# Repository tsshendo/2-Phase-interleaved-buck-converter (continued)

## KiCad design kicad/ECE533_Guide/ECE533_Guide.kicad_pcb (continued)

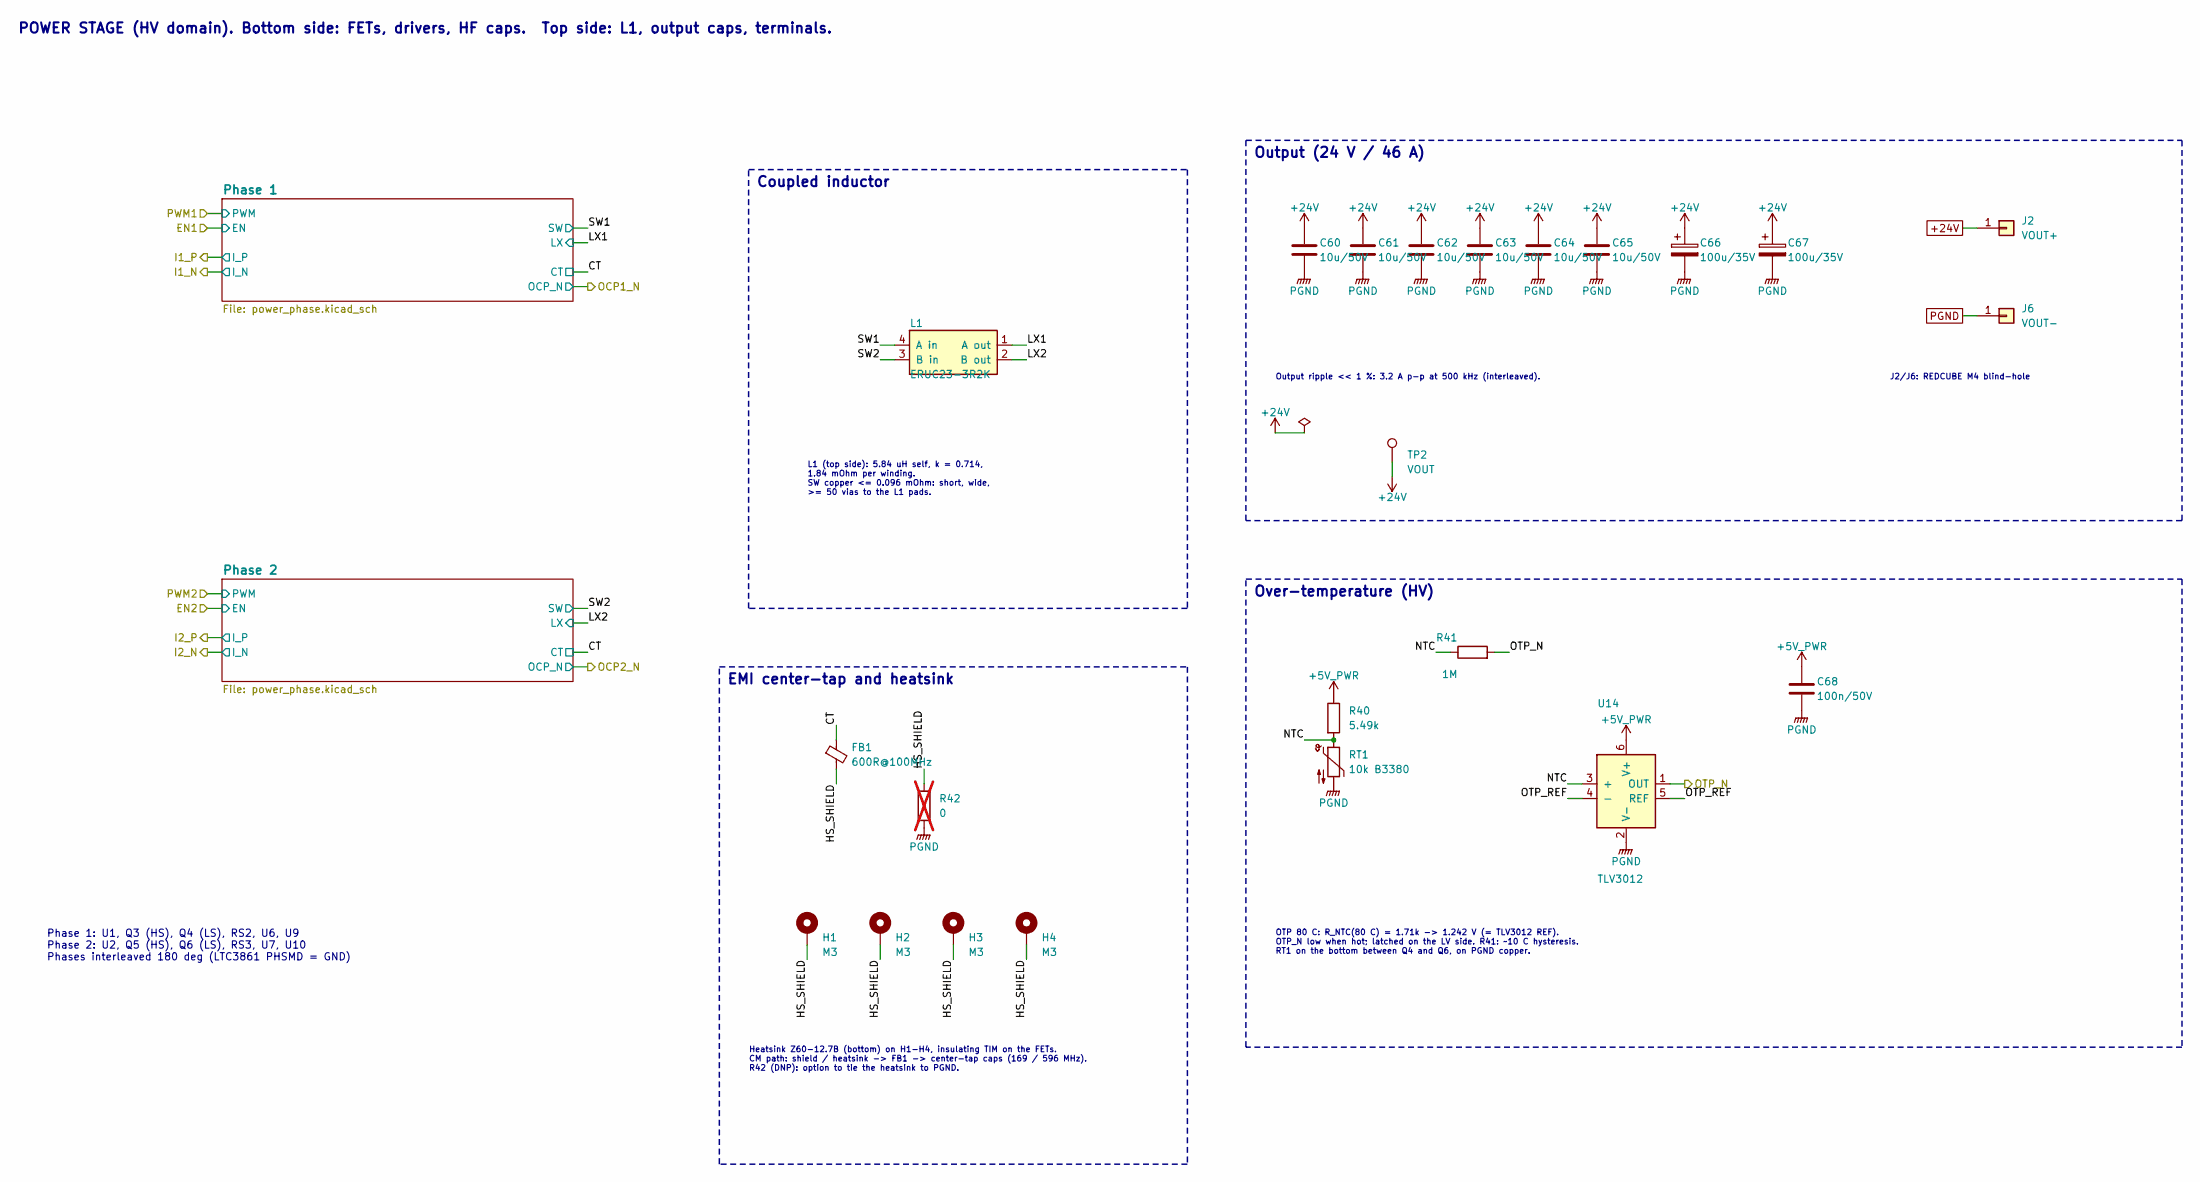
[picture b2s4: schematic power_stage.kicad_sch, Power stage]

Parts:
C60, C61, C62, C63, C64, C65: 10u/50V; C_1210_3225Metric; MPN GRM32ER71H106KA12L; LCSC C77102
C66, C67: 100u/35V; CP_Elec_8x10.5; MPN EEH-ZA1V101P
C68: 100n/50V; C_0603_1608Metric; MPN GRM188R71H104KA93D; LCSC C77055
FB1: 600R@100MHz; L_0603_1608Metric; MPN BLM18KG601SN1D; LCSC C85833
H1, H2, H3, H4: M3; MountingHole_3.2mm_M3_Pad_Via; MPN M3 plated hole
J2: VOUT+; Wurth_REDCUBE_74650194; MPN 74650194R
J6: VOUT-; Wurth_REDCUBE_74650194; MPN 74650194R
L1: ERUC23-3R2K; TDK_ERUC23; MPN ERUC23-3R2K
R40: 5.49k; R_0603_1608Metric; MPN RC0603FR-075K49L
R41: 1M; R_0603_1608Metric; MPN RC0603FR-071ML
R42: 0; R_0603_1608Metric; MPN RC0603JR-070RL; not fitted
RT1: 10k B3380; R_0603_1608Metric; MPN NCP18XH103F03RB; LCSC C13564
TP2: VOUT; TestPoint_Pad_D1.0mm; MPN Test pad (bare copper)
U14: TLV3012; SOT-23-6; MPN TLV3012AIDBVR; LCSC C62505

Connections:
+5V_PWR: C68.1, R40.1, U14.6 (V+); also elsewhere on the board
+24V: C60.1, C61.1, C62.1, C63.1, C64.1, C65.1, C66.1, C67.1, J2.1, TP2.1; also elsewhere on the board
/OTP_N: R41.2, U14.1 (OUT); also elsewhere on the board
/Power stage (2 phases)/CT: FB1.1; also elsewhere on the board
/Power stage (2 phases)/HS_SHIELD: FB1.2, H1.1, H2.1, H3.1, H4.1, R42.1
/Power stage (2 phases)/LX1: L1.1 (A out); also elsewhere on the board
/Power stage (2 phases)/LX2: L1.2 (B out); also elsewhere on the board
/Power stage (2 phases)/NTC: R40.2, R41.1, RT1.1, U14.3 (+)
/Power stage (2 phases)/OTP_REF: U14.4 (-), U14.5 (REF)
/Power stage (2 phases)/SW1: L1.4 (A in); also elsewhere on the board
/Power stage (2 phases)/SW2: L1.3 (B in); also elsewhere on the board
PGND: C60.2, C61.2, C62.2, C63.2, C64.2, C65.2, C66.2, C67.2, C68.2, J6.1, R42.2, RT1.2, U14.2 (V-); also elsewhere on the board

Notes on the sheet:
POWER STAGE (HV domain). Bottom side: FETs, drivers, HF caps. Top side: L1, output caps, terminals.
Phase 1: U1, Q3 (HS), Q4 (LS), RS2, U6, U9 Phase 2: U2, Q5 (HS), Q6 (LS), RS3, U7, U10 Phases interleaved 180 deg (LTC3861 PHSMD = GND)
L1 (top side): 5.84 uH self, k = 0.714, 1.84 mOhm per winding. SW copper <= 0.096 mOhm: short, wide, >= 50 vias to the L1 pads.
Coupled inductor
Output ripple << 1 %: 3.2 A p-p at 500 kHz (interleaved).
J2/J6: REDCUBE M4 blind-hole
Output (24 V / 46 A)
OTP 80 C: R_NTC(80 C) = 1.71k -> 1.242 V (= TLV3012 REF). OTP_N low when hot; latched on the LV side. R41: ~10 C hysteresis. RT1 on the bottom between Q4 and Q6, on PGND copper.
Over-temperature (HV)
Heatsink Z60-12.7B (bottom) on H1-H4, insulating TIM on the FETs. CM path: shield / heatsink -> FB1 -> center-tap caps (169 / 596 MHz). R42 (DNP): option to tie the heatsink to PGND.
EMI center-tap and heatsink

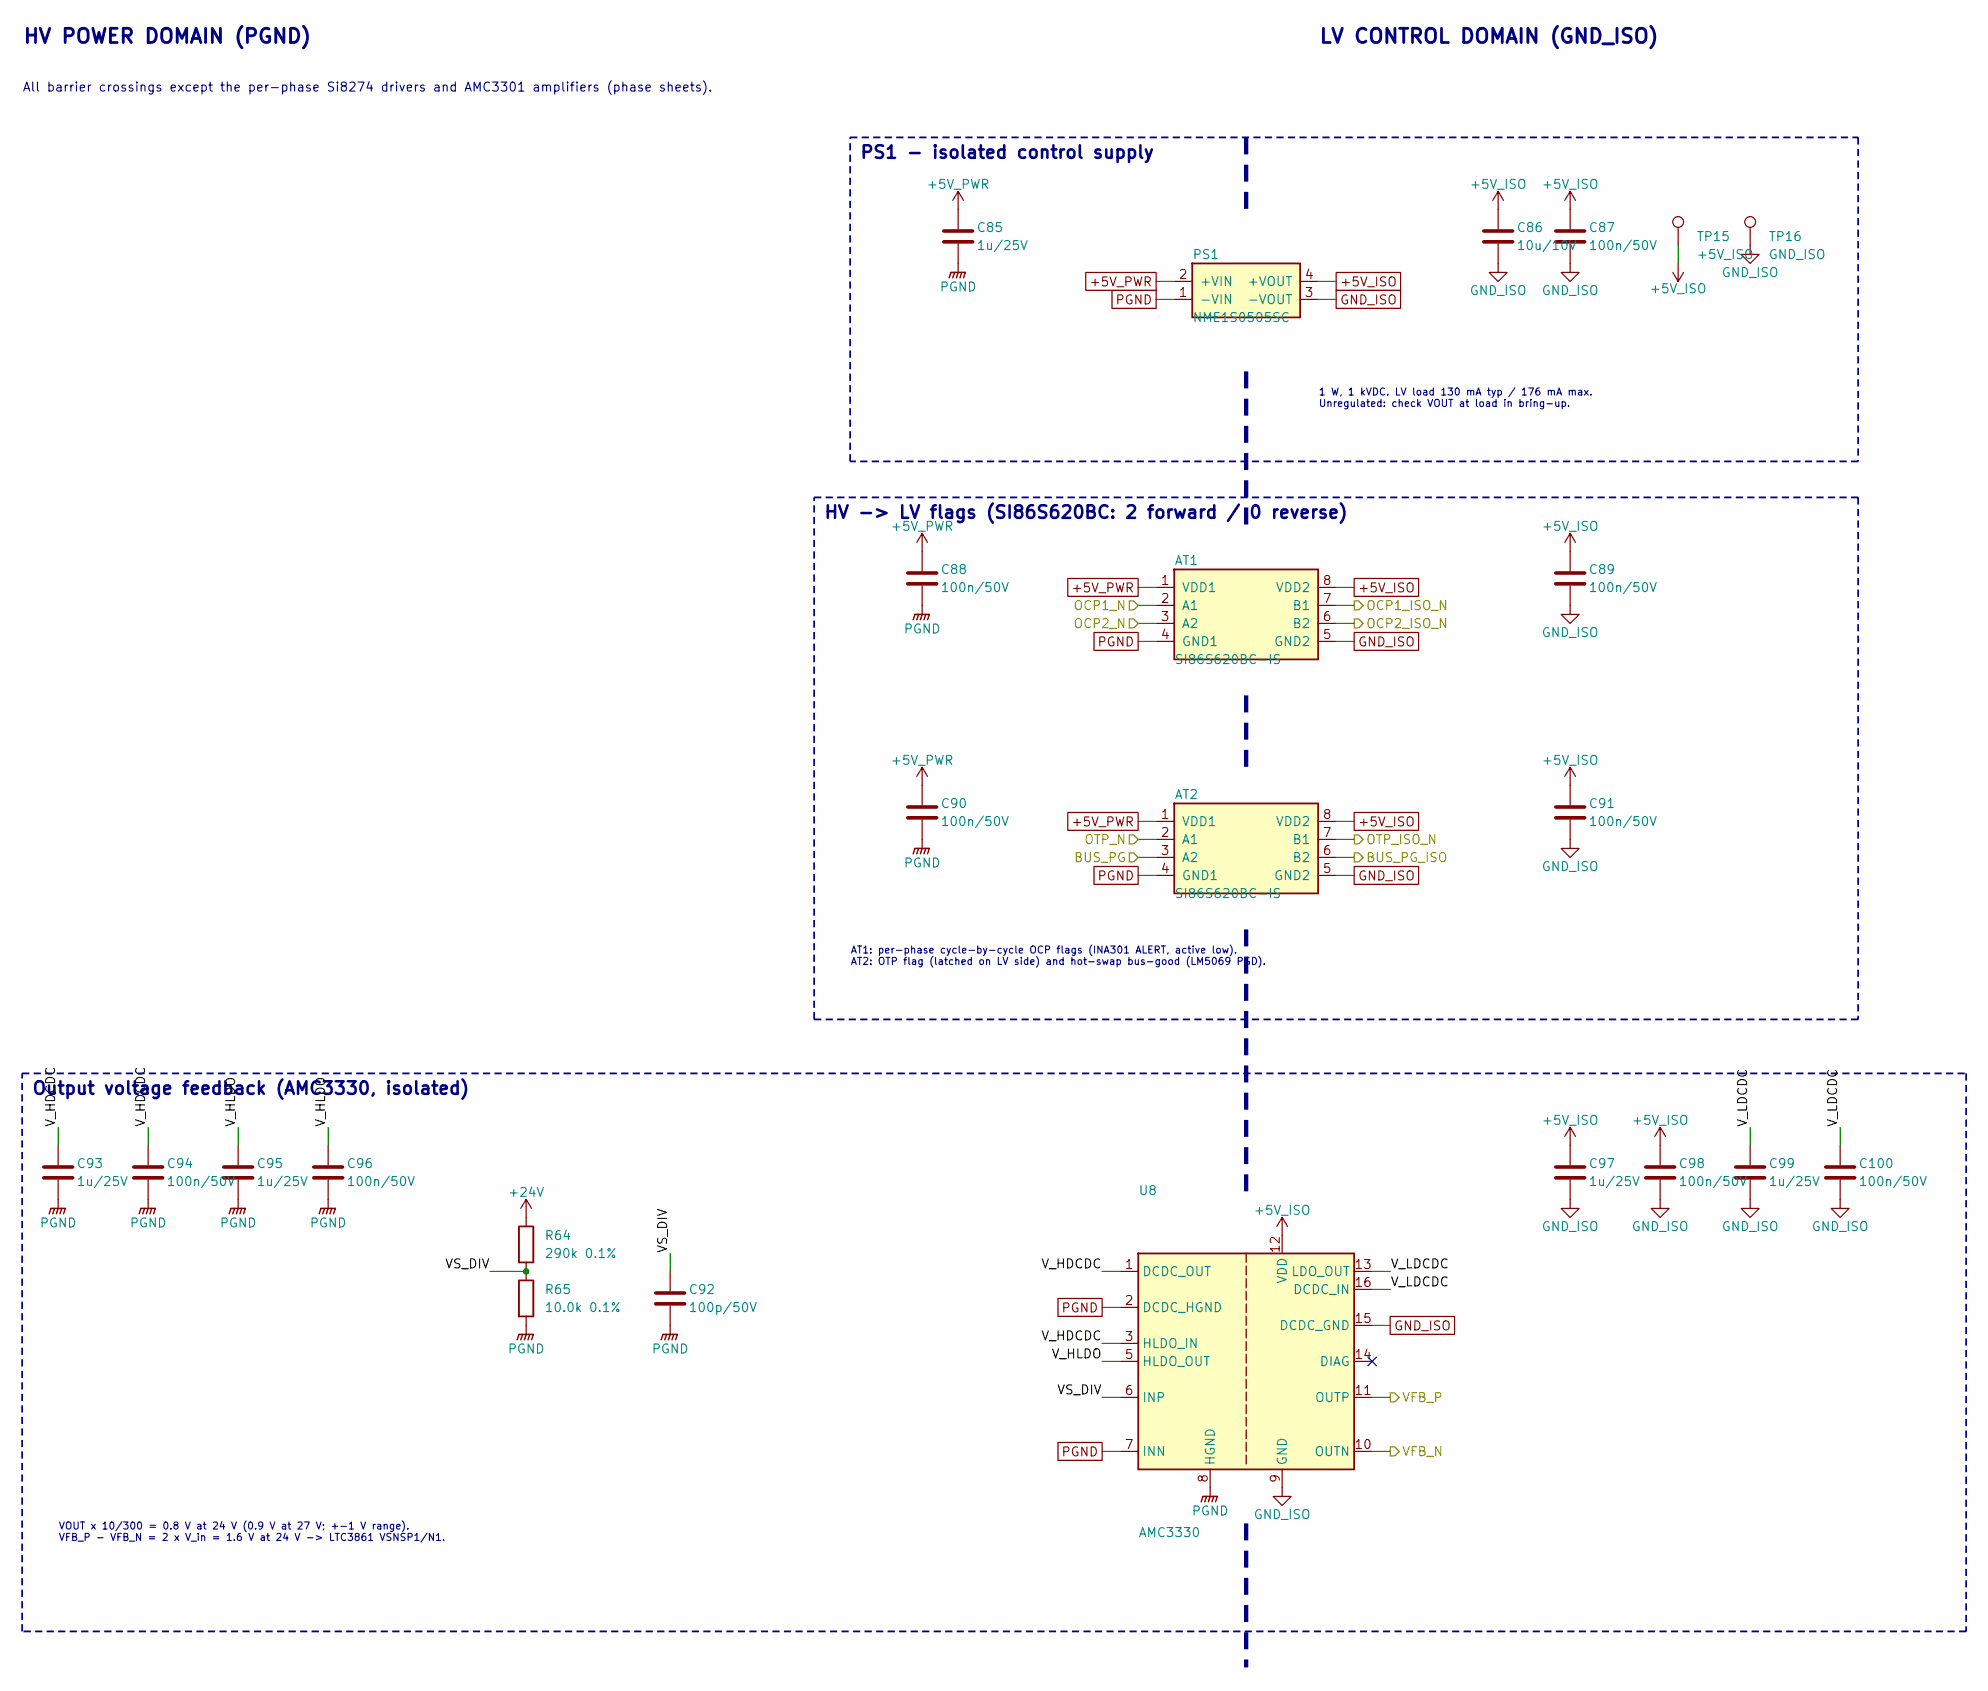
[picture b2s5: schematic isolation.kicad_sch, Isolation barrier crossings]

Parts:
AT1, AT2: SI86S620BC-IS; SOIC-8_3.9x4.9mm_P1.27mm; MPN SI86S620BC-IS; LCSC C7363570
C85, C93, C95, C97, C99: 1u/25V; C_0603_1608Metric; MPN GRM188R71E105KA12D; LCSC C86020
C86: 10u/10V; C_0805_2012Metric; MPN GRM21BR71A106KE51L; LCSC C86038
C87, C88, C89, C90, C91, C94, C96, C98, C100: 100n/50V; C_0603_1608Metric; MPN GRM188R71H104KA93D; LCSC C77055
C92: 100p/50V; C_0603_1608Metric; MPN GRM1885C1H101JA01D; LCSC C71664
PS1: NME1S0505SC; Murata_NME1S_SIP-4; MPN NME1S0505SC; LCSC C39128444
R64: 290k 0.1%; R_0603_1608Metric; MPN ERA-3AEB2903V
R65: 10.0k 0.1%; R_0603_1608Metric; MPN ERA-3AEB1002V
TP15: +5V_ISO; TestPoint_Pad_D1.0mm; MPN Test pad (bare copper)
TP16: GND_ISO; TestPoint_Pad_D1.0mm; MPN Test pad (bare copper)
U8: AMC3330; SOIC-16W_7.5x10.3mm_P1.27mm; MPN AMC3330DWER; LCSC C2999368

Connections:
+5V_ISO: AT1.8 (VDD2), AT2.8 (VDD2), C86.1, C87.1, C89.1, C91.1, C97.1, C98.1, PS1.4 (+VOUT), TP15.1, U8.12 (VDD); also elsewhere on the board
+5V_PWR: AT1.1 (VDD1), AT2.1 (VDD1), C85.1, C88.1, C90.1, PS1.2 (+VIN); also elsewhere on the board
+24V: R64.1; also elsewhere on the board
/BUS_PG: AT2.3 (A2); also elsewhere on the board
/BUS_PG_ISO: AT2.6 (B2); also elsewhere on the board
/Isolation barrier/VS_DIV: C92.1, R64.2, R65.1, U8.6 (INP)
/Isolation barrier/V_HDCDC: C93.1, C94.1, U8.1 (DCDC_OUT), U8.3 (HLDO_IN)
/Isolation barrier/V_HLDO: C95.1, C96.1, U8.5 (HLDO_OUT)
/Isolation barrier/V_LDCDC: C99.1, C100.1, U8.13 (LDO_OUT), U8.16 (DCDC_IN)
/OCP1_ISO_N: AT1.7 (B1); also elsewhere on the board
/OCP1_N: AT1.2 (A1); also elsewhere on the board
/OCP2_ISO_N: AT1.6 (B2); also elsewhere on the board
/OCP2_N: AT1.3 (A2); also elsewhere on the board
/OTP_ISO_N: AT2.7 (B1); also elsewhere on the board
/OTP_N: AT2.2 (A1); also elsewhere on the board
/VFB_N: U8.10 (OUTN); also elsewhere on the board
/VFB_P: U8.11 (OUTP); also elsewhere on the board
GND_ISO: AT1.5 (GND2), AT2.5 (GND2), C86.2, C87.2, C89.2, C91.2, C97.2, C98.2, C99.2, C100.2, PS1.3 (-VOUT), TP16.1, U8.9 (GND), U8.15 (DCDC_GND); also elsewhere on the board
PGND: AT1.4 (GND1), AT2.4 (GND1), C85.2, C88.2, C90.2, C92.2, C93.2, C94.2, C95.2, C96.2, PS1.1 (-VIN), R65.2, U8.2 (DCDC_HGND), U8.7 (INN), U8.8 (HGND); also elsewhere on the board

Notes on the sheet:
HV POWER DOMAIN (PGND)
LV CONTROL DOMAIN (GND_ISO)
All barrier crossings except the per-phase Si8274 drivers and AMC3301 amplifiers (phase sheets).
1 W, 1 kVDC. LV load 130 mA typ / 176 mA max. Unregulated: check VOUT at load in bring-up.
PS1 - isolated control supply
AT1: per-phase cycle-by-cycle OCP flags (INA301 ALERT, active low). AT2: OTP flag (latched on LV side) and hot-swap bus-good (LM5069 PGD).
HV -> LV flags (SI86S620BC: 2 forward / 0 reverse)
VOUT x 10/300 = 0.8 V at 24 V (0.9 V at 27 V; +-1 V range). VFB_P - VFB_N = 2 x V_in = 1.6 V at 24 V -> LTC3861 VSNSP1/N1.
Output voltage feedback (AMC3330, isolated)

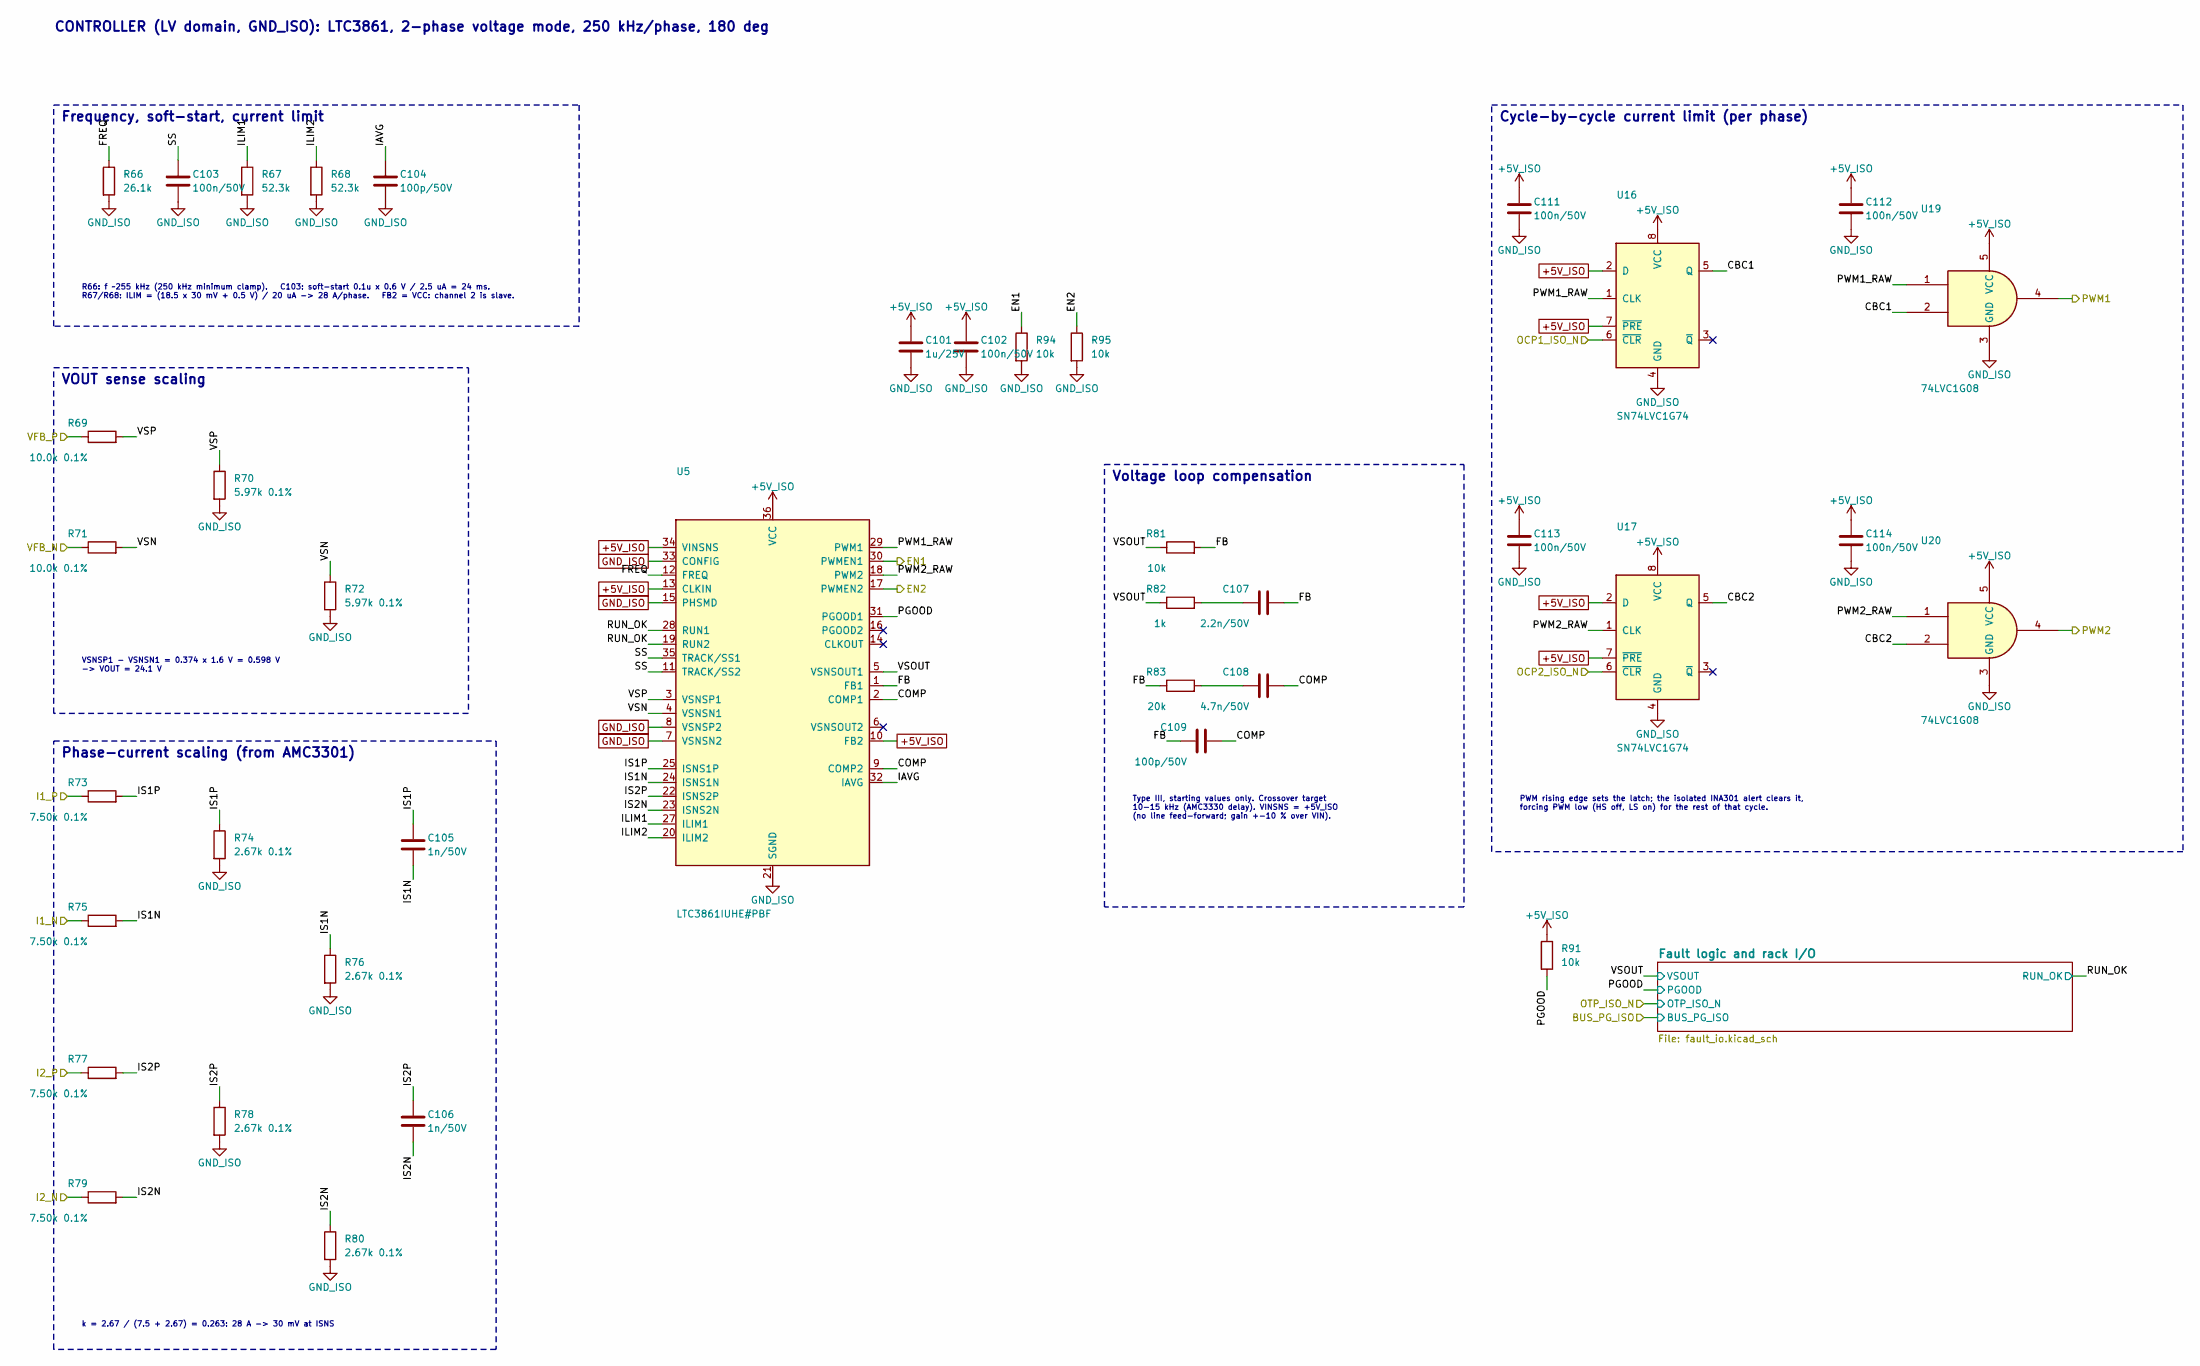
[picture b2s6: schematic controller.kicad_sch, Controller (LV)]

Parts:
C101: 1u/25V; C_0603_1608Metric; MPN GRM188R71E105KA12D; LCSC C86020
C102, C103, C111, C112, C113, C114: 100n/50V; C_0603_1608Metric; MPN GRM188R71H104KA93D; LCSC C77055
C104, C109: 100p/50V; C_0603_1608Metric; MPN GRM1885C1H101JA01D; LCSC C71664
C105, C106: 1n/50V; C_0603_1608Metric; MPN GRM1885C1H102JA01D; LCSC C77026
C107: 2.2n/50V; C_0603_1608Metric; MPN GRM188R71H222KA01D; LCSC C86023
C108: 4.7n/50V; C_0603_1608Metric; MPN GRM188R71H472KA01D; LCSC C77057
R66: 26.1k; R_0603_1608Metric; MPN RC0603FR-0726K1L
R67, R68: 52.3k; R_0603_1608Metric; MPN RC0603FR-0752K3L
R69, R71: 10.0k 0.1%; R_0603_1608Metric; MPN ERA-3AEB1002V
R70, R72: 5.97k 0.1%; R_0603_1608Metric; MPN ERA-3AEB5971V
R73, R75, R77, R79: 7.50k 0.1%; R_0603_1608Metric; MPN ERA-3AEB7501V
R74, R76, R78, R80: 2.67k 0.1%; R_0603_1608Metric; MPN ERA-3AEB2671V
R81, R91, R94, R95: 10k; R_0603_1608Metric; MPN RC0603FR-0710KL
R82: 1k; R_0603_1608Metric; MPN RC0603FR-071KL
R83: 20k; R_0603_1608Metric; MPN RC0603FR-0720KL
U5: LTC3861IUHE#PBF; QFN-36-1EP_5x6mm_P0.5mm_EP3.6x4.1mm; MPN LTC3861IUHE#PBF; LCSC C686466
U16, U17: SN74LVC1G74; SSOP-8_2.95x2.8mm_P0.65mm; MPN SN74LVC1G74DCTR; LCSC C840104
U19, U20: 74LVC1G08; SOT-23-5; MPN SN74LVC1G08DBVR; LCSC C7666

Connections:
+5V_ISO: C101.1, C102.1, C111.1, C112.1, C113.1, C114.1, R91.1, U5.10 (FB2), U5.13 (CLKIN), U5.34 (VINSNS), U5.36 (VCC), U16.2 (D), U16.7 (~PRE), U16.8 (VCC), U17.2 (D), U17.7 (~PRE), U17.8 (VCC), U19.5 (VCC), U20.5 (VCC); also elsewhere on the board
/Controller (LV)/CBC1: U16.5 (Q), U19.2
/Controller (LV)/CBC2: U17.5 (Q), U20.2
/Controller (LV)/COMP: C108.2, C109.2, U5.2 (COMP1), U5.9 (COMP2)
/Controller (LV)/FB: C107.2, C109.1, R81.2, R83.1, U5.1 (FB1)
/Controller (LV)/FREQ: R66.1, U5.12 (FREQ)
/Controller (LV)/IAVG: C104.1, U5.32 (IAVG)
/Controller (LV)/ILIM1: R67.1, U5.27 (ILIM1)
/Controller (LV)/ILIM2: R68.1, U5.20 (ILIM2)
/Controller (LV)/IS1N: C105.2, R75.2, R76.1, U5.24 (ISNS1N)
/Controller (LV)/IS1P: C105.1, R73.2, R74.1, U5.25 (ISNS1P)
/Controller (LV)/IS2N: C106.2, R79.2, R80.1, U5.23 (ISNS2N)
/Controller (LV)/IS2P: C106.1, R77.2, R78.1, U5.22 (ISNS2P)
/Controller (LV)/PGOOD: R91.2, U5.31 (PGOOD1); also elsewhere on the board
/Controller (LV)/PWM1_RAW: U5.29 (PWM1), U16.1 (CLK), U19.1
/Controller (LV)/PWM2_RAW: U5.18 (PWM2), U17.1 (CLK), U20.1
/Controller (LV)/RUN_OK: U5.19 (RUN2), U5.28 (RUN1); also elsewhere on the board
/Controller (LV)/SS: C103.1, U5.11 (TRACK/SS2), U5.35 (TRACK/SS1)
/Controller (LV)/VSN: R71.2, R72.1, U5.4 (VSNSN1)
/Controller (LV)/VSOUT: R81.1, R82.1, U5.5 (VSNSOUT1); also elsewhere on the board
/Controller (LV)/VSP: R69.2, R70.1, U5.3 (VSNSP1)
/EN1: R94.1, U5.30 (PWMEN1); also elsewhere on the board
/EN2: R95.1, U5.17 (PWMEN2); also elsewhere on the board
/I1_N: R75.1; also elsewhere on the board
/I1_P: R73.1; also elsewhere on the board
/I2_N: R79.1; also elsewhere on the board
/I2_P: R77.1; also elsewhere on the board
/OCP1_ISO_N: U16.6 (~CLR); also elsewhere on the board
/OCP2_ISO_N: U17.6 (~CLR); also elsewhere on the board
/PWM1: U19.4; also elsewhere on the board
/PWM2: U20.4; also elsewhere on the board
/VFB_N: R71.1; also elsewhere on the board
/VFB_P: R69.1; also elsewhere on the board
GND_ISO: C101.2, C102.2, C103.2, C104.2, C111.2, C112.2, C113.2, C114.2, R66.2, R67.2, R68.2, R70.2, R72.2, R74.2, R76.2, R78.2, R80.2, R94.2, R95.2, U5.7 (VSNSN2), U5.8 (VSNSP2), U5.15 (PHSMD), U5.21 (SGND), U5.26 (SGND), U5.33 (CONFIG), U5.37 (SGND), U16.4 (GND), U17.4 (GND), U19.3 (GND), U20.3 (GND); also elsewhere on the board
unnamed: C107.1, R82.2
unnamed: C108.1, R83.2

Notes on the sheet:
CONTROLLER (LV domain, GND_ISO): LTC3861, 2-phase voltage mode, 250 kHz/phase, 180 deg
R66: f ~255 kHz (250 kHz minimum clamp). C103: soft-start 0.1u x 0.6 V / 2.5 uA = 24 ms. R67/R68: ILIM = (18.5 x 30 mV + 0.5 V) / 20 uA -> 28 A/phase. FB2 = VCC: channel 2 is slave.
Frequency, soft-start, current limit
VSNSP1 - VSNSN1 = 0.374 x 1.6 V = 0.598 V -> VOUT = 24.1 V
VOUT sense scaling
k = 2.67 / (7.5 + 2.67) = 0.263: 28 A -> 30 mV at ISNS
Phase-current scaling (from AMC3301)
Type III, starting values only. Crossover target 10-15 kHz (AMC3330 delay). VINSNS = +5V_ISO (no line feed-forward; gain +-10 % over VIN).
Voltage loop compensation
PWM rising edge sets the latch; the isolated INA301 alert clears it, forcing PWM low (HS off, LS on) for the rest of that cycle.
Cycle-by-cycle current limit (per phase)
